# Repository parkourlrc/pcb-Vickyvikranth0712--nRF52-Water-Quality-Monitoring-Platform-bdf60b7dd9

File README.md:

# AquaSense – nRF52 Water Quality Monitoring Platform

---

# Overview

AquaSense is a low-power embedded hardware platform designed for modular water quality monitoring applications.

The project is built around the **E73-2G4M04S1B (nRF52832)** Bluetooth Low Energy module and provides a compact battery-powered platform capable of interfacing with multiple external water quality sensors through dedicated JST connectors.

The primary objective of this project was to design a production-style embedded PCB while following industry-standard design practices including:

- Hierarchical schematics
- Modular subsystem design
- IPC-based PCB routing decisions
- Net class management
- RF layout considerations
- Manufacturing-ready outputs

---

# Features

- nRF52832 BLE module (E73-2G4M04S1B)
- USB Type-C power input
- MCP73831 Li-Ion battery charger
- MCP1700 3.3V Low Dropout Regulator
- Battery-powered operation
- SWD programming/debug interface
- Modular JST sensor connectors
- Dedicated ground plane
- RF antenna keep-out region
- Manufacturing-ready Gerbers
- Two-layer PCB

---

# Hardware Architecture

```
                USB Type-C
                     │
                     ▼
              MCP73831 Charger
                     │
                     ▼
             Li-Ion Battery Cell
                     │
                     ▼
              MCP1700 LDO (3.3V)
                     │
        ┌────────────┴────────────┐
        │                         │
        ▼                         ▼
  E73-2G4M04S1B             Status LED
 (nRF52832 BLE Module)
        │
        ├──────────── SWD
        ├──────────── UART
        ├──────────── pH Connector
        ├──────────── TDS Connector
        ├──────────── Turbidity Connector
        └──────────── DS18B20 Connector
```

---

# PCB Specifications

| Parameter | Value |
|------------|-------|
| Layers | 2 |
| PCB Thickness | 1.6 mm |
| Copper Weight | 1 oz |
| Ground Plane | Bottom Layer |
| Manufacturing | Standard 2-layer FR4 |
| Design Software | KiCad 10 |

---

# Components

| Component | Description |
|------------|------------|
| E73-2G4M04S1B | BLE Module (nRF52832) |
| MCP73831 | Li-Ion Battery Charger |
| MCP1700 | 3.3V LDO Regulator |
| USB Type-C | Power Input |
| JST Connectors | External Sensor Interfaces |
| SW Push Button | Reset |
| LED | Status Indicator |

---

# Sensor Interfaces

The PCB is designed to support modular external sensor modules.

Supported interfaces include:

- pH Sensor
- TDS Sensor
- Turbidity Sensor
- DS18B20 Temperature Sensor

Sensor modules are connected through JST headers, allowing flexibility for future sensor upgrades without redesigning the PCB.

---

# Design Decisions

Some of the major engineering decisions made during the design process include:

- Hierarchical schematic architecture
- Bottom-layer GND plane
- Dedicated RF antenna keep-out region
- USB Type-C used only for power input
- MCP73831 configured for approximately 256 mA charging current
- Modular JST sensor connectors
- Power trace widths selected using IPC-2152 calculations with additional engineering margin
- Net classes created for Power, Battery, Analog, Digital and SWD signals

---

# Project Structure

```
nRF52-Water-Quality-Monitoring-Platform/

├── docs/
│   ├── Architecture.md
│   ├── Component_Selection.md
│   ├── Design_Decisions.md
│   ├── Requirements.md
│   └── Revision_History.md
│
├── hardware/
│   ├── Datasheets/
│   ├── KiCad_Project/
│   └── Libraries/
│
├── manufacturing/
│   ├── BOM/
│   ├── Drill/
│   ├── Gerbers/
│   
├── images/
│   ├── PCB/
│   ├── 3D/
│   └── Schematics/
│
├── README.md
└── LICENSE
```

---

# PCB Images

## PCB Layout

> 

## Ground Plane

> 

## 3D Front

> 

---

## 3D Back

> 

# Design Verification

The hardware design has been verified through:

- Electrical Rules Check (ERC)
- Design Rules Check (DRC)
- Manufacturing rule validation
- IPC-guided power trace sizing
- RF keep-out verification
- Gerber generation
- Drill file generation

---

# Manufacturing Outputs

The repository includes:

- Gerber Files
- Excellon Drill Files
- Bill of Materials (CSV)

These outputs are suitable for fabrication using standard PCB manufacturers.

---

# Future Improvements

Future hardware revisions may include:

- Integrated sensor circuitry
- Battery fuel gauge
- Reverse polarity protection
- Lower standby power consumption
- Four-layer PCB revision
- Environmental enclosure integration

---

# Tools Used

- KiCad 10
- Saturn PCB Toolkit
- Git
- GitHub

---

# License

This project is released under the MIT License.

See the LICENSE file for details.

---

# Author

**Vikranth V**

Electronics and Communication Engineering  
SRM Institute of Science and Technology

GitHub: https://github.com/Vickyvikranth0712

LinkedIn: https://www.linkedin.com/in/vikranth1012/

---

⭐ If you found this project interesting, consider starring the repository.

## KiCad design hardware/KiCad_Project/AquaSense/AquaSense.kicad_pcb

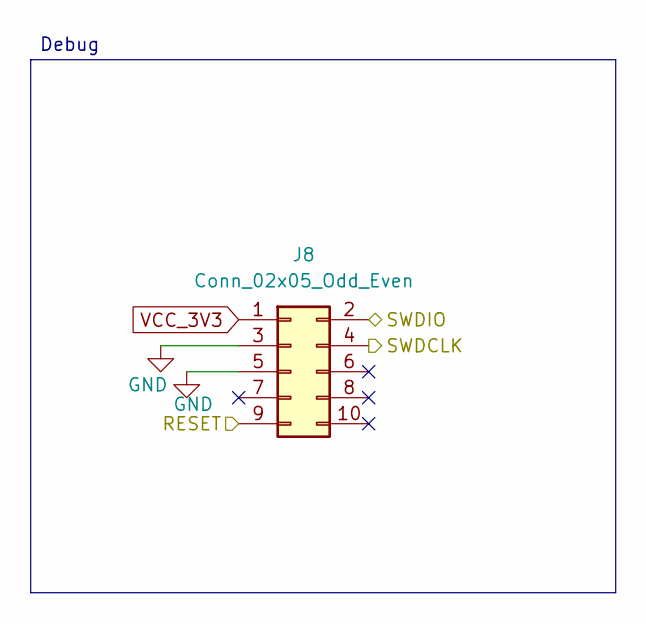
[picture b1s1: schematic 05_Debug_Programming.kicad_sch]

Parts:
J8: Conn_02x05_Odd_Even; PinHeader_2x05_P1.27mm_Vertical

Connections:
/Debug_Programming/RESET: J8.9; also elsewhere on the board
/Debug_Programming/SWDCLK: J8.4; also elsewhere on the board
/Debug_Programming/SWDIO: J8.2; also elsewhere on the board
GND: J8.3, J8.5; also elsewhere on the board
VCC_3V3: J8.1; also elsewhere on the board

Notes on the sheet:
Debug

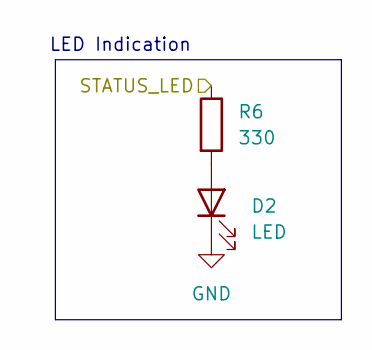
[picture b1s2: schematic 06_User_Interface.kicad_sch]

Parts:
D2: LED; LED_0603_1608Metric
R6: 330; R_0603_1608Metric

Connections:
/User_Interface/STATUS_LED: R6.1; also elsewhere on the board
GND: D2.1 (K); also elsewhere on the board
unnamed: D2.2 (A), R6.2

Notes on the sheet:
LED Indication

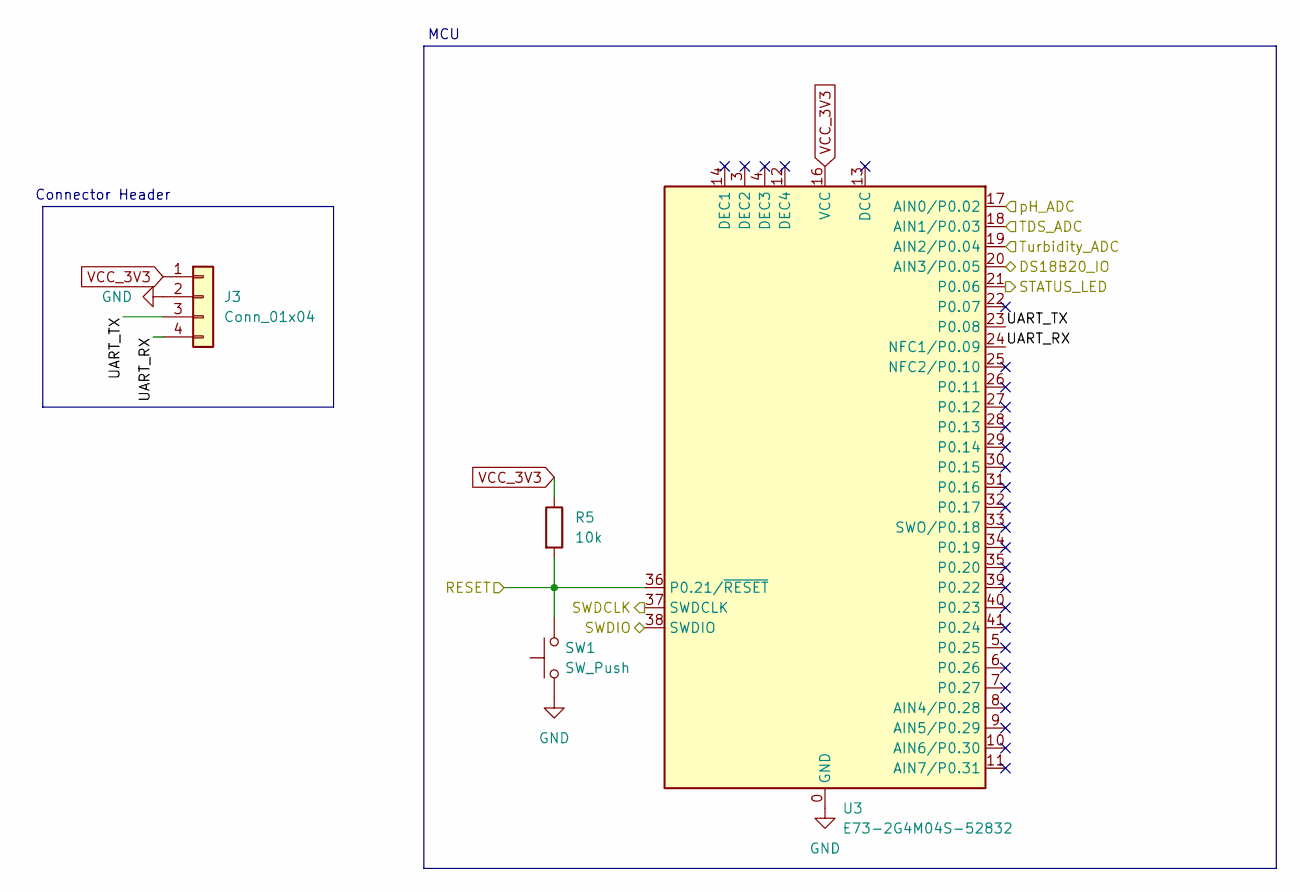
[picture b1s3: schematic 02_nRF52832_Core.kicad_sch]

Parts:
J3: Conn_01x04; PinHeader_1x04_P2.54mm_Vertical
R5: 10k; R_0603_1608Metric
SW1: SW_Push; SW_SPST_SKQG_WithoutStem
U3: E73-2G4M04S-52832; E73-2G4M04S

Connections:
/Debug_Programming/RESET: R5.2, SW1.2, U3.36 (P0.21/~RESET); also elsewhere on the board
/Debug_Programming/SWDCLK: U3.37 (SWDCLK); also elsewhere on the board
/Debug_Programming/SWDIO: U3.38 (SWDIO); also elsewhere on the board
/Sensor_Interfaces/DS18B20_IO: U3.20 (AIN3/P0.05); also elsewhere on the board
/Sensor_Interfaces/TDS_ADC: U3.18 (AIN1/P0.03); also elsewhere on the board
/Sensor_Interfaces/Turbidity_ADC: U3.19 (AIN2/P0.04); also elsewhere on the board
/Sensor_Interfaces/pH_ADC: U3.17 (AIN0/P0.02); also elsewhere on the board
/User_Interface/STATUS_LED: U3.21 (P0.06); also elsewhere on the board
/nRF52832_Core/UART_RX: J3.4, U3.24 (NFC1/P0.09)
/nRF52832_Core/UART_TX: J3.3, U3.23 (P0.08)
GND: J3.2, SW1.1, U3.0 (GND), U3.1 (GND), U3.2 (GND), U3.15 (GND), U3.42 (GND), U3.43 (GND); also elsewhere on the board
VCC_3V3: J3.1, R5.1, U3.16 (VCC); also elsewhere on the board

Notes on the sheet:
Connector Header
MCU

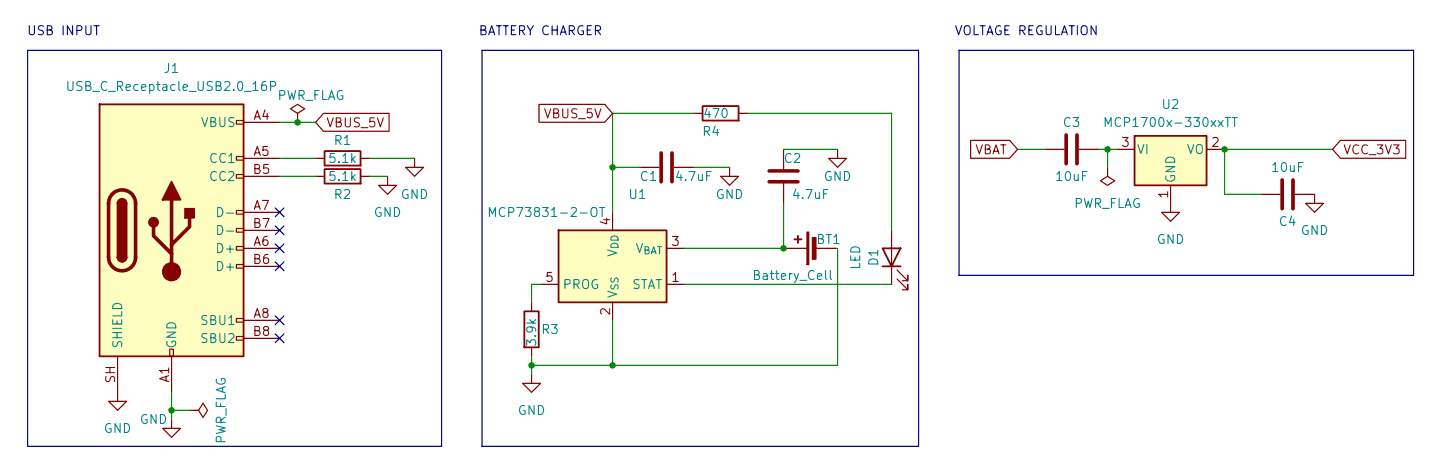
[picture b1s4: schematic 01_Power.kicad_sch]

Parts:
BT1: Battery_Cell; JST_PH_B2B-PH-K_1x02_P2.00mm_Vertical
C1, C2: 4.7uF; C_0603_1608Metric
C3, C4: 10uF; C_0603_1608Metric
D1: LED; LED_0603_1608Metric
J1: USB_C_Receptacle_USB2.0_16P; USB_C_Receptacle_HRO_TYPE-C-31-M-12
R1, R2: 5.1k; R_0603_1608Metric
R3: 3.9k; R_0603_1608Metric
R4: 470; R_0603_1608Metric
U1: MCP73831-2-OT; SOT-23-5
U2: MCP1700x-330xxTT; SOT-23

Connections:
GND: BT1.2 (-), C1.2, C2.2, C4.2, J1.A1 (GND), J1.A12 (GND), J1.B1 (GND), J1.B12 (GND), J1.SH (SHIELD), R1.2, R2.2, R3.2, U1.2 (V_{SS}), U2.1 (GND); also elsewhere on the board
unnamed: BT1.1 (+), C2.1, U1.3 (V_{BAT})
unnamed: D1.2 (A), R4.2
unnamed: D1.1 (K), U1.1 (STAT)
unnamed: J1.A5 (CC1), R1.1
unnamed: J1.B5 (CC2), R2.1
unnamed: R3.1, U1.5 (PROG)
unnamed: C3.2, U2.3 (VI)
VBAT: C3.1
VBUS_5V: C1.1, J1.A4 (VBUS), J1.A9 (VBUS), J1.B4 (VBUS), J1.B9 (VBUS), R4.1, U1.4 (V_{DD})
VCC_3V3: C4.1, U2.2 (VO); also elsewhere on the board

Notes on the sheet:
VOLTAGE REGULATION
USB INPUT
BATTERY CHARGER

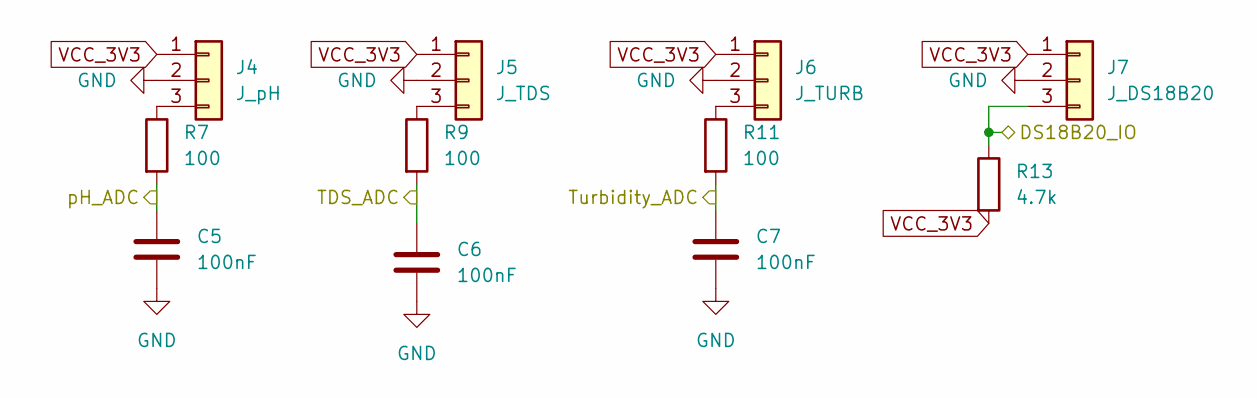
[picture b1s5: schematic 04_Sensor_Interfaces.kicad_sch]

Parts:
C5, C6, C7: 100nF; C_0603_1608Metric
J4: J_pH; JST_PH_B3B-PH-K_1x03_P2.00mm_Vertical
J5: J_TDS; JST_PH_B3B-PH-K_1x03_P2.00mm_Vertical
J6: J_TURB; JST_PH_B3B-PH-K_1x03_P2.00mm_Vertical
J7: J_DS18B20; JST_PH_B3B-PH-K_1x03_P2.00mm_Vertical
R7, R9, R11: 100; R_0603_1608Metric
R13: 4.7k; R_0603_1608Metric

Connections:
/Sensor_Interfaces/DS18B20_IO: J7.3, R13.1; also elsewhere on the board
/Sensor_Interfaces/TDS_ADC: C6.1, R9.2; also elsewhere on the board
/Sensor_Interfaces/Turbidity_ADC: C7.1, R11.2; also elsewhere on the board
/Sensor_Interfaces/pH_ADC: C5.1, R7.2; also elsewhere on the board
GND: C5.2, C6.2, C7.2, J4.2, J5.2, J6.2, J7.2; also elsewhere on the board
unnamed: J4.3, R7.1
unnamed: J5.3, R9.1
unnamed: J6.3, R11.1
VCC_3V3: J4.1, J5.1, J6.1, J7.1, R13.2; also elsewhere on the board

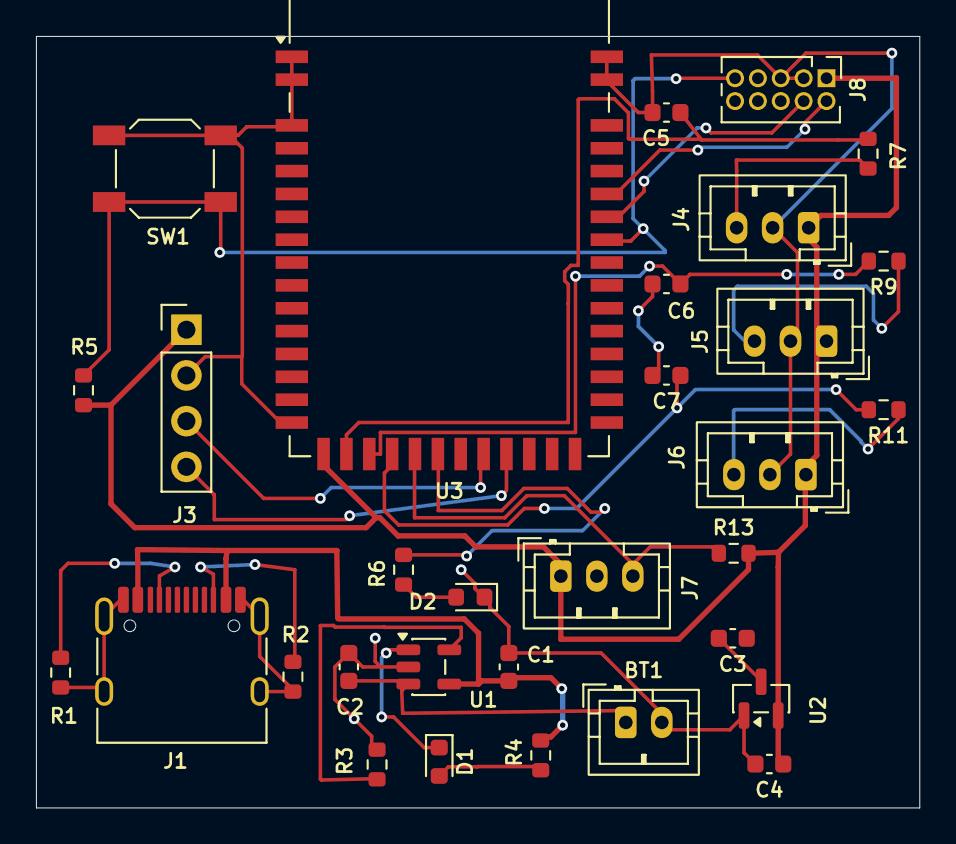
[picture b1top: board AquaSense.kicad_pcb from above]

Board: 2 copper layers, 49.1 x 42.9 mm, 31 parts (0 on the bottom side), 24 nets.

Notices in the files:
README.md:
License: MIT
